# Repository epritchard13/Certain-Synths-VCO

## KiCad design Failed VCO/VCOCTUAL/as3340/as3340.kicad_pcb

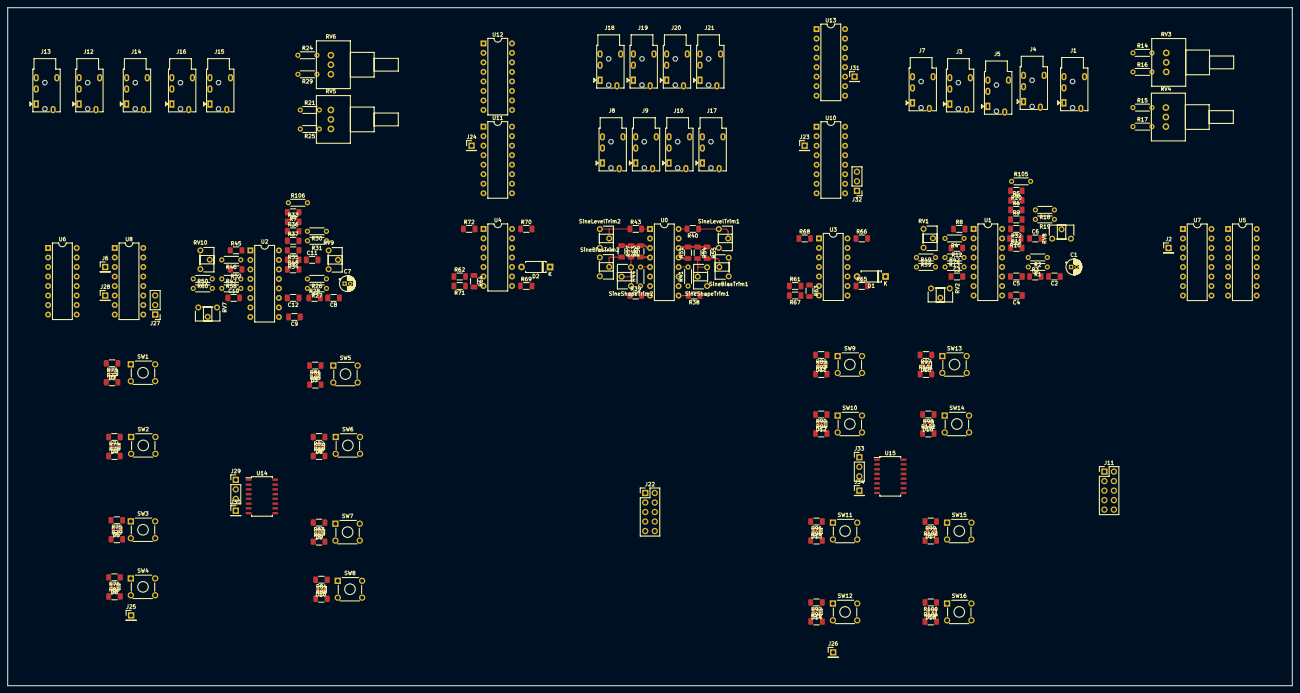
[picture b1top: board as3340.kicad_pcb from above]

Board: 2 copper layers, 342.9 x 181.0 mm, 215 parts (0 on the bottom side), 178 nets.

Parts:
C1, C7: 100nf; CP_Radial_D4.0mm_P1.50mm
C2, C6, C8, C11: 10nf; C_1206_3216Metric_Pad1.33x1.80mm_HandSolder
C3, C4, C5, C9, C10, C12: 1nf; C_1206_3216Metric_Pad1.33x1.80mm_HandSolder
D1, D2: DIODE; D_A-405_P7.62mm_Horizontal
D3, D4, D5, D6, D7, D8, D9, D10, D11, D12, D13, D14, D15, D16, D17, D18: LD271; LED_0603_1608Metric
J1, J15: LinearFMInput; Jack_3.5mm_PJ320E_Horizontal
J2, J6, J23, J24, J25, J26, J28, J30, J31, J34: Conn_01x01_Male; PinHeader_1x01_P2.54mm_Vertical
J3, J13: HardSyncInput; Jack_3.5mm_PJ320E_Horizontal
J4, J14: SoftSyncInput; Jack_3.5mm_PJ320E_Horizontal
J5, J16: CV1; Jack_3.5mm_PJ320E_Horizontal
J7, J12: PWM Input; Jack_3.5mm_PJ320E_Horizontal
J8, J18: SQR OUT; Jack_3.5mm_PJ320E_Horizontal
J9, J19: SAW OUT; Jack_3.5mm_PJ320E_Horizontal
J10, J20: TRI OUT; Jack_3.5mm_PJ320E_Horizontal
J11, J22: Conn_02x05_Odd_Even; PinHeader_2x05_P2.54mm_Vertical
J17, J21: SIN OUT; Jack_3.5mm_PJ320E_Horizontal
J27, J29, J32, J33: Conn_01x03_Male; PinHeader_1x03_P2.54mm_Vertical
R1, R18, R27, R30, R41, R44, R105, R106: 1M; R_Axial_DIN0204_L3.6mm_D1.6mm_P5.08mm_Horizontal
R2, R26: 1.5M; R_Axial_DIN0204_L3.6mm_D1.6mm_P5.08mm_Horizontal
R3, R10, R28, R34, R73, R74, R75, R76, R81, R82, R83, R84, R89, R90, R91, R92, R97, R98, R99, R100: 470; R_1206_3216Metric_Pad1.30x1.75mm_HandSolder
R4, R46: 5.6k; R_Axial_DIN0204_L3.6mm_D1.6mm_P5.08mm_Horizontal
R5, R6, R7, R9, R20, R33, R36, R37, R40, R43, R61, R62, R63, R64: 100k; R_1206_3216Metric_Pad1.30x1.75mm_HandSolder
R8, R45: 24k; R_1206_3216Metric_Pad1.30x1.75mm_HandSolder
R11, R48: 1.8k; R_1206_3216Metric_Pad1.30x1.75mm_HandSolder
R12, R52: 910; R_1206_3216Metric_Pad1.30x1.75mm_HandSolder
R13, R58: 2k; R_Axial_DIN0204_L3.6mm_D1.6mm_P5.08mm_Horizontal
R14, R21: 10k; R_Axial_DIN0204_L3.6mm_D1.6mm_P5.08mm_Horizontal
R15, R17, R19, R24, R29, R31: 100k; R_Axial_DIN0204_L3.6mm_D1.6mm_P5.08mm_Horizontal
R16, R25, R42, R47, R49, R50, R59, R60: 47k; R_Axial_DIN0204_L3.6mm_D1.6mm_P5.08mm_Horizontal
R32, R35: 200k; R_1206_3216Metric_Pad1.30x1.75mm_HandSolder
R38, R39: 4.7k; R_1206_3216Metric_Pad1.30x1.75mm_HandSolder
R51, R53, R65, R66, R67, R68, R69, R70, R71, R72: 1k; R_1206_3216Metric_Pad1.30x1.75mm_HandSolder
R54, R56: 20k; R_1206_3216Metric_Pad1.30x1.75mm_HandSolder
R55, R57: 470k; R_1206_3216Metric_Pad1.30x1.75mm_HandSolder
R77, R78, R79, R80, R85, R86, R87, R88, R93, R94, R95, R96, R101, R102, R103, R104: 10k; R_1206_3216Metric_Pad1.30x1.75mm_HandSolder
RV1, RV7, RV10: 10k Pot; Potentiometer_ACP_CA6-H2,5_Horizontal
RV2: 20k Pot; Potentiometer_ACP_CA6-H2,5_Horizontal
RV3, RV4, RV5, RV6: 100kPot; Potentiometer_Vishay_148-149_Single_Horizontal
RV8, RV9: 100k Pot; Potentiometer_ACP_CA6-H2,5_Horizontal
SW1, SW2, SW3, SW4, SW5, SW6, SW7, SW8, SW9, SW10, SW11, SW12, SW13, SW14, SW15, SW16: SW_DIP_x01; SW_TH_Tactile_Omron_B3F-10xx
SineBiasTrim1, SineBiasTrim2: 100k Pot; Potentiometer_ACP_CA6-H2,5_Horizontal
SineLevelTrim1, SineLevelTrim2: 1M Pot; Potentiometer_ACP_CA6-H2,5_Horizontal
SineShapeTrim1, SineShapeTrim2: 100k Pot; Potentiometer_ACP_CA6-H2,5_Horizontal
U0: LM13700; DIP-16_W7.62mm
U1, U2: AS3340; DIP-16_W7.62mm
U3, U4: LM324; DIP-14_W7.62mm
U5, U6, U12, U13: 74ls189; DIP-16_W7.62mm
U7, U8, U10, U11: 74HC4051; DIP-16_W7.62mm
U14, U15: 74LS138; SOIC-16W_5.3x10.2mm_P1.27mm

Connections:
+5V: J22.9, R73.2, R74.2, R75.2, R76.2, R77.1, R78.1, R79.1, R80.1, R81.2, R82.2, R83.2, R84.2, R85.1, R86.1, R87.1, R88.1, R89.2, R90.2, R91.2, R92.2, R93.1, R94.1, R95.1, R96.1, R97.2, R98.2, R99.2, R100.2, R101.1, R102.1, R103.1, R104.1, U5.16 (VCC), U6.16 (VCC), U7.16 (VCC), U8.16 (VCC), U10.16 (VCC), U11.16 (VCC), U12.16 (VCC), U13.16 (VCC), U14.16 (VCC), U15.16 (VCC)
+15V: J11.9, J11.10, R2.1, R16.2, R17.2, R25.2, R26.1, R29.2, R41.1, R44.1, RV8.3, RV9.3, SineBiasTrim1.3, SineBiasTrim2.3, SineLevelTrim1.3, SineLevelTrim2.3, U0.7, U0.10, U0.11 (V+), U1.16 (VCC), U2.16 (VCC), U3.4 (V+), U4.4 (V+)
-15V: J11.1, J11.2, R12.2, R14.1, R15.1, R21.1, R24.1, R38.1, R39.1, R52.2, SineBiasTrim1.1, SineBiasTrim2.1, U0.6 (V-), U3.11 (V-), U4.11 (V-)
GND: C2.1, C5.1, C6.2, C8.1, C11.2, C12.1, D1.1 (K), D2.1 (K), J1.S, J3.S, J4.S, J5.S, J7.S, J8.S, J9.S, J10.S, J11.3, J11.4, J11.5, J11.6, J11.7, J11.8, J12.S, J13.S, J14.S, J15.S, J16.S, J17.S, J18.S, J19.S, J20.S, J21.S, J22.2, R11.2, R48.2, R49.2, R50.2, R59.2, R60.2, R61.1, R62.1, RV2.3, RV7.3, U1.12 (GND), U2.12 (GND), U5.1 (A0), U5.2 (~CS), U5.8 (GND), U5.13 (A3), U5.14 (A2), U5.15 (A1), U6.1 (A0), U6.2 (~CS), U6.8 (GND), U6.13 (A3), U6.14 (A2), U6.15 (A1), U7.7 (VEE), U7.8 (GND), U8.7 (VEE), U8.8 (GND), U10.7 (VEE), U10.8 (GND), U11.7 (VEE), U11.8 (GND), U12.1 (A0), U12.2 (~CS), U12.8 (GND), U12.13 (A3), U12.14 (A2), U12.15 (A1), U13.1 (A0), U13.2 (~CS), U13.8 (GND), U13.13 (A3), U13.14 (A2), U13.15 (A1), U14.4 (E1), U14.5 (E2), U14.8 (GND), U15.4 (E1), U15.5 (E2), U15.8 (GND)
unnamed: C1.1, R1.1
unnamed: C1.2, J1.T, U7.15 (A2), U8.15 (A2)
unnamed: C2.2, R3.2
unnamed: C3.1, J3.T, U7.14 (A1), U8.14 (A1)
unnamed: C3.2, U1.6 (VHSI)
unnamed: C4.1, J4.T
unnamed: C4.2, U1.9 (VSSI)
unnamed: C5.2, U1.11 (CAP)
unnamed: C6.1, R10.1
unnamed: C7.1, R27.1
unnamed: C7.2, J15.T, U7.2 (A6), U8.2 (A6)
unnamed: C8.2, R28.2
unnamed: C9.1, J14.T
unnamed: C9.2, U2.9 (VSSI)
unnamed: C10.1, J13.T, U7.5 (A5), U8.5 (A5)
unnamed: C10.2, U2.6 (VHSI)
unnamed: C11.1, R34.1
unnamed: C12.2, U2.11 (CAP)
unnamed: D1.2 (A), R13.2, R59.1, U3.10 (+)
unnamed: D2.2 (A), R58.2, R60.1, U4.10 (+)
unnamed: D3.1 (K), SW1.1, U14.15 (O0)
unnamed: D3.2 (A), R73.1
unnamed: D4.1 (K), SW2.1, U14.14 (O1)
unnamed: D4.2 (A), R74.1
unnamed: D5.1 (K), SW3.1, U14.13 (O2)
unnamed: D5.2 (A), R75.1
unnamed: D6.1 (K), SW4.1, U14.12 (O3)
unnamed: D6.2 (A), R76.1
unnamed: D7.1 (K), SW5.1, U14.11 (O4)
unnamed: D7.2 (A), R81.1
unnamed: D8.1 (K), SW6.1, U14.10 (O5)
unnamed: D8.2 (A), R82.1
unnamed: D9.1 (K), SW7.1, U14.9 (O6)
unnamed: D9.2 (A), R83.1
unnamed: D10.1 (K), SW8.1, U14.7 (O7)
unnamed: D10.2 (A), R84.1
unnamed: D11.1 (K), SW9.1, U15.15 (O0)
unnamed: D11.2 (A), R89.1
unnamed: D12.1 (K), SW10.1, U15.14 (O1)
unnamed: D12.2 (A), R90.1
unnamed: D13.1 (K), SW11.1, U15.13 (O2)
unnamed: D13.2 (A), R91.1
unnamed: D14.1 (K), SW12.1, U15.12 (O3)
unnamed: D14.2 (A), R92.1
unnamed: D15.1 (K), SW13.1, U15.11 (O4)
unnamed: D15.2 (A), R97.1
unnamed: D16.1 (K), SW14.1, U15.10 (O5)
unnamed: D16.2 (A), R98.1
unnamed: D17.1 (K), SW15.1, U15.9 (O6)
unnamed: D17.2 (A), R99.1
unnamed: D18.1 (K), SW16.1, U15.7 (O7)
unnamed: D18.2 (A), R100.1
unnamed: J2.1, U7.3 (A)
unnamed: J5.T, R5.2
unnamed: J6.1, U8.3 (A)
unnamed: J7.T, R42.1, U7.13 (A0), U8.13 (A0)
unnamed: J8.T, R65.2, U10.4 (A7), U11.4 (A7)
unnamed: J9.T, R66.2, U10.2 (A6), U11.2 (A6)
unnamed: J10.T, R67.2, U10.5 (A5), U11.5 (A5)
unnamed: J12.T, R47.1, U7.1 (A4), U8.1 (A4)
unnamed: J16.T, R33.2
unnamed: J17.T, R68.2, U10.1 (A4), U11.1 (A4)
unnamed: J18.T, R69.2, U10.12 (A3), U11.12 (A3)
unnamed: J19.T, R70.2, U10.15 (A2), U11.15 (A2)
unnamed: J20.T, R71.2, U10.14 (A1), U11.14 (A1)
unnamed: J21.T, R72.2, U10.13 (A0), U11.13 (A0)
unnamed: J22.1, U12.3 (~WE)
unnamed: J22.3, U6.3 (~WE)
unnamed: J22.4, U5.12 (D4), U6.12 (D4), U12.12 (D4), U13.12 (D4)
unnamed: J22.5, U13.3 (~WE)
unnamed: J22.6, U5.10 (D3), U6.10 (D3), U12.10 (D3), U13.10 (D3)
unnamed: J22.7, U5.3 (~WE)
unnamed: J22.8, U5.6 (D2), U6.6 (D2), U12.6 (D2), U13.6 (D2)
unnamed: J22.10, U5.4 (D1), U6.4 (D1), U12.4 (D1), U13.4 (D1)
unnamed: J23.1, U10.3 (A)
unnamed: J24.1, U11.3 (A)
unnamed: J25.1, R77.2, R78.2, R79.2, R80.2, R85.2, R86.2, R87.2, R88.2, SW1.2, SW2.2, SW3.2, SW4.2, SW5.2, SW6.2, SW7.2, SW8.2
unnamed: J26.1, R93.2, R94.2, R95.2, R96.2, R101.2, R102.2, R103.2, R104.2, SW9.2, SW10.2, SW11.2, SW12.2, SW13.2, SW14.2, SW15.2, SW16.2
unnamed: J27.1, U6.9 (~Y3), U8.9 (S2)
unnamed: J27.2, U6.7 (~Y2), U8.10 (S1)
unnamed: J27.3, U6.5 (~Y1), U8.11 (S0)
unnamed: J28.1, U6.11 (~Y4), U8.6 (~E)
unnamed: J29.1, U14.1 (A0)
unnamed: J29.2, U14.2 (A1)
unnamed: J29.3, U14.3 (A2)
unnamed: J30.1, U14.6 (E3)
unnamed: J31.1, U10.6 (~E), U13.11 (~Y4)
unnamed: J32.1, U10.9 (S2), U13.9 (~Y3)
unnamed: J32.2, U10.10 (S1), U13.7 (~Y2)
unnamed: J32.3, U10.11 (S0), U13.5 (~Y1)
unnamed: J33.1, U15.1 (A0)
unnamed: J33.2, U15.2 (A1)
unnamed: J33.3, U15.3 (A2)
unnamed: J34.1, U15.6 (E3)
unnamed: R1.2, R2.2, R3.1, U1.13 (VLFI)
unnamed: R4.2, U1.2 (SCALE2)
unnamed: R7.1, U7.4 (A7), U8.4 (A7)
unnamed: R8.1, RV1.1
unnamed: R8.2, U1.1 (SCALE1)
unnamed: R5.1, R6.1, R9.1, R10.2, R20.2, R32.2, R105.1, U1.15 (VFCI)
unnamed: R11.1, U1.14 (VS)
unnamed: R4.1, R12.1, RV1.2, RV1.3, U1.3 (VEE)
unnamed: R13.1, U1.4 (VP)
unnamed: R14.2, RV3.3
unnamed: R15.2, RV4.3
unnamed: R16.1, RV3.1
unnamed: R17.1, RV4.1
unnamed: R18.1, RV4.2
unnamed: R6.2, R18.2
unnamed: R19.1, RV3.2
unnamed: R9.2, R19.2
unnamed: R20.1, U7.12 (A3), U8.12 (A3)
unnamed: R21.2, RV5.3
unnamed: R24.2, RV6.3
unnamed: R25.1, RV5.1
unnamed: R26.2, R27.2, R28.1, U2.13 (VLFI)
unnamed: R29.1, RV6.1
unnamed: R30.1, RV6.2
unnamed: R30.2, R36.2
unnamed: R31.1, RV5.2
unnamed: R31.2, R37.2
unnamed: R32.1, RV8.1, RV8.2
unnamed: R7.2, R33.1, R34.2, R35.2, R36.1, R37.1, R106.1, U2.15 (VFCI)
unnamed: R35.1, RV9.1, RV9.2
unnamed: R39.2, U0.8, U4.3 (+)
unnamed: R40.1, SineLevelTrim1.1, SineLevelTrim1.2
unnamed: R40.2, U0.16
unnamed: R41.2, U0.12
unnamed: R42.2, R49.1, U1.5 (VPWM)
unnamed: R43.1, SineLevelTrim2.1, SineLevelTrim2.2
unnamed: R43.2, U0.1
unnamed: R44.2, U0.5
unnamed: R45.1, RV10.1
unnamed: R45.2, U2.1 (SCALE1)
unnamed: R46.1, R52.1, RV10.2, RV10.3, U2.3 (VEE)
unnamed: R46.2, U2.2 (SCALE2)
unnamed: R47.2, R50.1, U2.5 (VPWM)
unnamed: R48.1, U2.14 (VS)
unnamed: R51.1, U0.13 (-)
unnamed: R51.2, R54.1, R55.1, U0.14 (+)
unnamed: R53.1, U0.4 (-)
unnamed: R53.2, R56.1, R57.1, U0.3 (+)
unnamed: R54.2, SineShapeTrim1.2, SineShapeTrim1.3
unnamed: R55.2, SineBiasTrim1.2
unnamed: R56.2, SineShapeTrim2.2, SineShapeTrim2.3
unnamed: R57.2, SineBiasTrim2.2
unnamed: R58.1, U2.4 (VP)
unnamed: R61.2, R63.1, U3.6 (-)
unnamed: R62.2, R64.1, U4.6 (-)
unnamed: R63.2, R67.1, SineShapeTrim1.1, U3.7
unnamed: R64.2, R71.1, SineShapeTrim2.1, U4.7
unnamed: R65.1, U3.8, U3.9 (-)
unnamed: R66.1, U3.13 (-), U3.14
unnamed: R68.1, U3.1, U3.2 (-)
unnamed: R69.1, U4.8, U4.9 (-)
unnamed: R70.1, U4.13 (-), U4.14
unnamed: R72.1, U4.1, U4.2 (-)
unnamed: RV2.1, U1.7 (VHFT)
unnamed: R105.2, RV2.2
unnamed: RV7.1, U2.7 (VHFT)
unnamed: R106.2, RV7.2
unnamed: U1.8 (VSO), U3.12 (+)
unnamed: U1.10 (VTO), U3.5 (+)
unnamed: U2.8 (VSO), U4.12 (+)
unnamed: U2.10 (VTO), U4.5 (+)
unnamed: R38.2, U0.9, U3.3 (+)
unnamed: U5.5 (~Y1), U7.11 (S0)
unnamed: U5.7 (~Y2), U7.10 (S1)
unnamed: U5.9 (~Y3), U7.9 (S2)
unnamed: U5.11 (~Y4), U7.6 (~E)
unnamed: U11.6 (~E), U12.11 (~Y4)
unnamed: U11.9 (S2), U12.9 (~Y3)
unnamed: U11.10 (S1), U12.7 (~Y2)
unnamed: U11.11 (S0), U12.5 (~Y1)

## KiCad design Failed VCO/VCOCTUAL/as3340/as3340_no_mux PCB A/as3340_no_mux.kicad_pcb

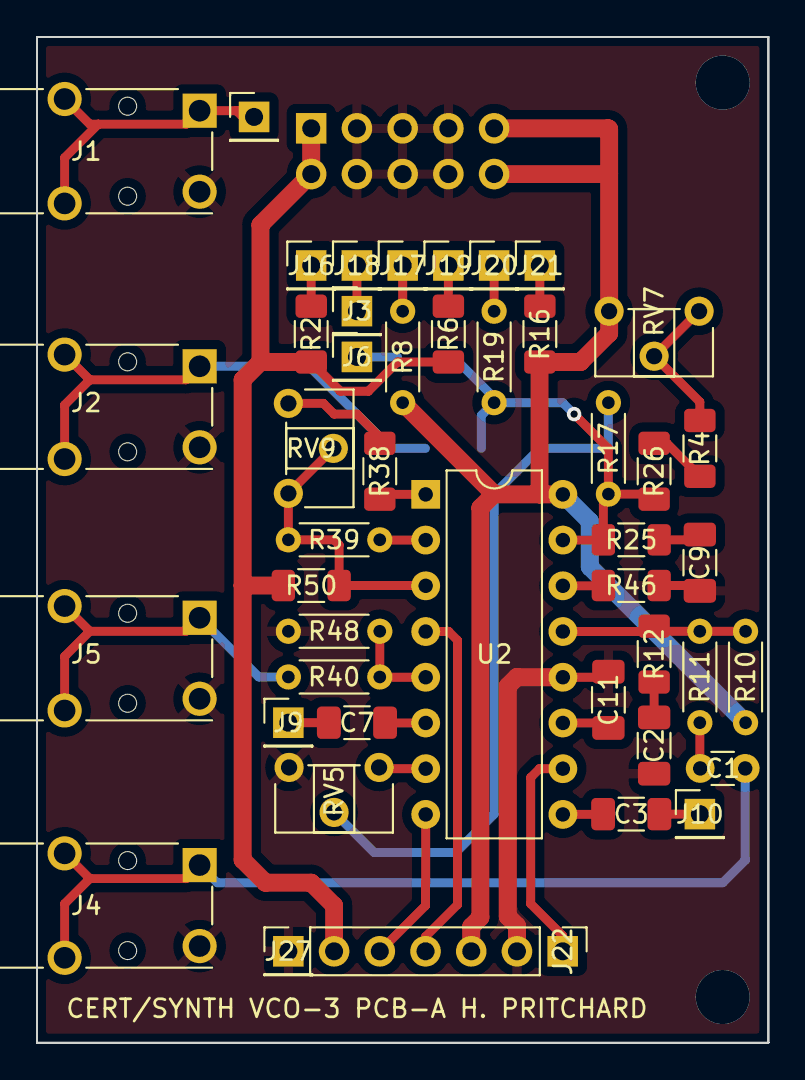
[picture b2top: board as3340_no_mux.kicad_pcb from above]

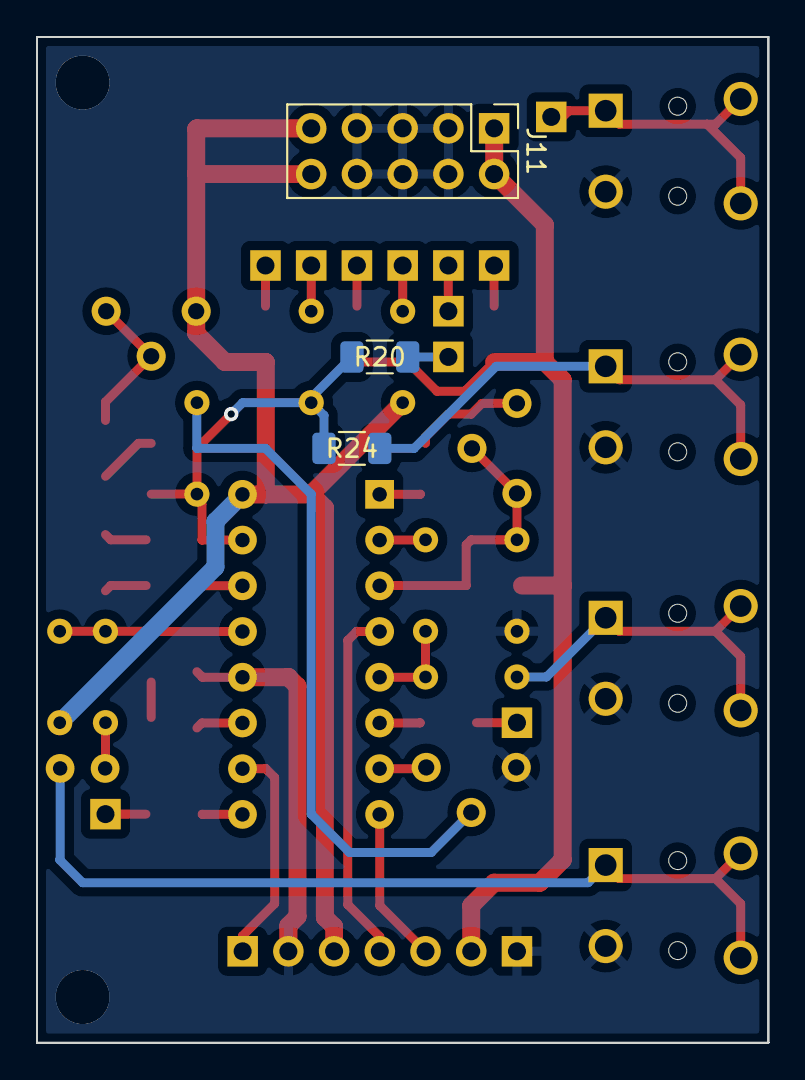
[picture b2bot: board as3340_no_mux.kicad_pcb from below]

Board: 2 copper layers, 40.6 x 55.9 mm, 48 parts (3 on the bottom side), 37 nets.

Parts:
C1: 100nf; C_Disc_D3.0mm_W1.6mm_P2.50mm
C2, C9: 10nf; C_1206_3216Metric_Pad1.33x1.80mm_HandSolder
C3, C7, C11: 1nf; C_1206_3216Metric_Pad1.33x1.80mm_HandSolder
J1: Sync INput; Jack_3.5mm_Switronic_ST-005-G_horizontal
J2: CV1; Jack_3.5mm_Switronic_ST-005-G_horizontal
J3, J6, J9, J10, J16, J17, J18, J19, J20, J21, J25, J27: Conn_01x01_Male; PinHeader_1x01_P2.54mm_Vertical
J4: LinearFmINput; Jack_3.5mm_Switronic_ST-005-G_horizontal
J5: PWM INput; Jack_3.5mm_Switronic_ST-005-G_horizontal
J11: Conn_02x05_Odd_Even; PinHeader_2x05_P2.54mm_Vertical
J22: Conn_01x06_Female; PinHeader_1x06_P2.54mm_Vertical
R2: 10k; R_1206_3216Metric_Pad1.30x1.75mm_HandSolder
R4, R6, R16, R20, R24, R26: 100k; R_1206_3216Metric_Pad1.30x1.75mm_HandSolder
R8, R40, R48: 47k; R_Axial_DIN0204_L3.6mm_D1.6mm_P5.08mm_Horizontal
R10: 1.5M; R_Axial_DIN0204_L3.6mm_D1.6mm_P5.08mm_Horizontal
R11, R17, R19: 1M; R_Axial_DIN0204_L3.6mm_D1.6mm_P5.08mm_Horizontal
R12, R25: 470; R_1206_3216Metric_Pad1.30x1.75mm_HandSolder
R38: 24k; R_1206_3216Metric_Pad1.30x1.75mm_HandSolder
R39: 5.6k; R_Axial_DIN0204_L3.6mm_D1.6mm_P5.08mm_Horizontal
R46: 1.8k; R_1206_3216Metric_Pad1.30x1.75mm_HandSolder
R50: 910; R_1206_3216Metric_Pad1.30x1.75mm_HandSolder
RV5: 20k Pot; Potentiometer_ACP_CA6-H2,5_Horizontal
RV7: 100k TrimPot; Potentiometer_ACP_CA6-H2,5_Horizontal
RV9: 10k Pot; Potentiometer_ACP_CA6-H2,5_Horizontal
U2: AS3340; DIP-16_W7.62mm

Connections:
+15V: J11.9, J11.10, J22.3, R8.2, R10.1, R16.2, RV7.3, U2.16 (VCC)
-15V: J11.1, J11.2, J22.6, R2.1, R6.1, R50.2
GND: C2.1, C9.2, C11.1, J1.S, J2.S, J4.S, J5.S, J11.3, J11.4, J11.5, J11.6, J11.7, J11.8, J22.2, J27.1, R46.2, R48.2, RV5.3, U2.12 (GND)
unnamed: C1.1, R11.1
unnamed: C1.2, J4.R, J4.T
unnamed: C2.2, R12.2
unnamed: C3.1, J10.1
unnamed: C3.2, U2.9 (VSSI)
unnamed: C7.1, J9.1
unnamed: C7.2, U2.6 (VHSI)
unnamed: C9.1, R25.1
unnamed: C11.2, U2.11 (CAP)
unnamed: J1.R, J1.T, J25.1
unnamed: J3.1, J18.1
unnamed: J22.1, U2.10 (VTO)
unnamed: J22.4, U2.4 (VP)
unnamed: J22.5, U2.8 (VSO)
unnamed: J16.1, R2.2
unnamed: J19.1, R6.2
unnamed: J17.1, R8.1
unnamed: R10.2, R11.2, R12.1, U2.13 (VLFI)
unnamed: J21.1, R16.1
unnamed: R17.1, R19.2, R20.2, R24.1, R25.2, R26.2, U2.15 (VFCI)
unnamed: R17.2, RV5.2
unnamed: J20.1, R19.1
unnamed: J6.1, R20.1
unnamed: J2.R, J2.T, R24.2
unnamed: R4.2, R26.1
unnamed: R38.1, RV9.1
unnamed: R38.2, U2.1 (SCALE1)
unnamed: R39.1, R50.1, RV9.2, RV9.3, U2.3 (VEE)
unnamed: R39.2, U2.2 (SCALE2)
unnamed: J5.R, J5.T, R40.1
unnamed: R40.2, R48.1, U2.5 (VPWM)
unnamed: R46.1, U2.14 (VS)
unnamed: RV5.1, U2.7 (VHFT)
unnamed: R4.1, RV7.1, RV7.2

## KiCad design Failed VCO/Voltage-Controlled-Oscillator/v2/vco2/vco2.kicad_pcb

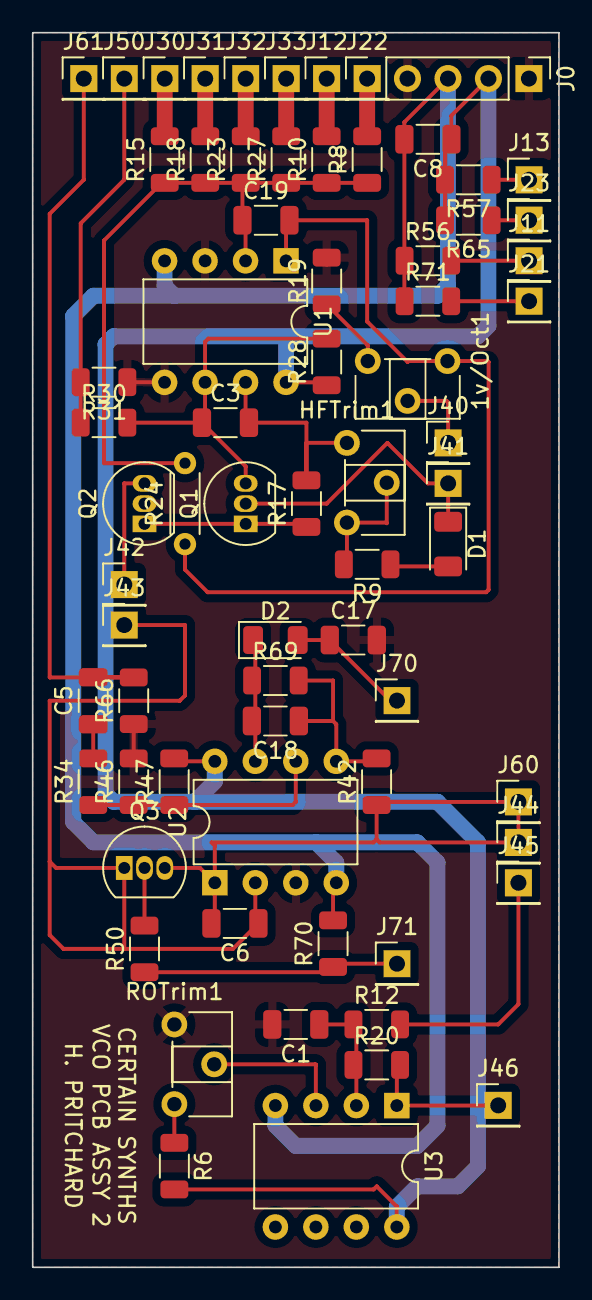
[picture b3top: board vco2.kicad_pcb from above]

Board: 2 copper layers, 33.0 x 77.5 mm, 70 parts (0 on the bottom side), 37 nets.

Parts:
1v/Oct1: 100; Potentiometer_ACP_CA6-H2,5_Horizontal
C1: 0.1uF; C_1206_3216Metric
C3, C17, C19: 100pF; C_1206_3216Metric
C5: 0.001uF; C_1206_3216Metric
C6: 0.005uF; C_1206_3216Metric
C8: .1uF; C_1206_3216Metric
C18: 4.7pF; C_1206_3216Metric
D1, D2: DIODE; D_1206_3216Metric
HFTrim1: 100k; Potentiometer_ACP_CA6-H2,5_Horizontal
J0: P; PinHeader_1x04_P2.54mm_Vertical
J11: TP1-; PinHeader_1x01_P2.54mm_Vertical
J12: P1; PinHeader_1x01_P2.54mm_Vertical
J13: TP1+; PinHeader_1x01_P2.54mm_Vertical
J21: TP2-; PinHeader_1x01_P2.54mm_Vertical
J22: P2; PinHeader_1x01_P2.54mm_Vertical
J23: TP2+; PinHeader_1x01_P2.54mm_Vertical
J30, J31, J32, J33: CV; PinHeader_1x01_P2.54mm_Vertical
J40: LINOUT; PinHeader_1x01_P2.54mm_Vertical
J41: LININ; PinHeader_1x01_P2.54mm_Vertical
J42: EXPOUT; PinHeader_1x01_P2.54mm_Vertical
J43: EXPIN; PinHeader_1x01_P2.54mm_Vertical
J44: RAWOUT; PinHeader_1x01_P2.54mm_Vertical
J45: RAWIN; PinHeader_1x01_P2.54mm_Vertical
J46: RAMPOUT; PinHeader_1x01_P2.54mm_Vertical
J50: LA; PinHeader_1x01_P2.54mm_Vertical
J60: RAW; PinHeader_1x01_P2.54mm_Vertical
J61: S; PinHeader_1x01_P2.54mm_Vertical
J70, J71: JUMPER00; PinHeader_1x01_P2.54mm_Vertical
Q1, Q2, Q3: 2N3904; TO-92_Inline
R6, R10, R15, R18, R23, R27, R31, R50, R66: 100k; R_1206_3216Metric
R8, R28, R30, R69: 1M; R_1206_3216Metric
R9: 4.7k; R_1206_3216Metric
R12, R17, R42, R47, R71: 10k; R_1206_3216Metric
R19: 475; R_1206_3216Metric
R20, R65: 47k; R_1206_3216Metric
R24: 100k TEMPCO; R_Axial_DIN0204_L3.6mm_D1.6mm_P5.08mm_Horizontal
R34: 1k; R_1206_3216Metric
R46: 2k; R_1206_3216Metric
R56, R57: 200k; R_1206_3216Metric
R70: 18k; R_1206_3216Metric
ROTrim1: 10k; Potentiometer_ACP_CA6-H2,5_Horizontal
U1, U2, U3: LM358; DIP-8_W7.62mm

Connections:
+12V: C6.1, C8.1, J0.2, J42.1, J43.1, J46.1, Q2.3 (C), Q3.1 (E), R6.2, R20.2, R28.1, R47.2, R57.2, R65.2, U1.8 (V+), U2.2 (-), U2.8 (V+), U3.1, U3.8 (V+)
-12V: C8.2, J0.3, R56.1, R70.2, R71.1, U1.4 (V-), U2.4 (V-), U3.4 (V-)
GND: C1.2, C17.2, J0.1, J0.4, Q2.2 (B), R19.2, R31.1, R46.2, R66.1, ROTrim1.1, U1.3 (+), U1.5 (+), U2.3 (+)
unnamed: C5.2, J61.1, R66.2
unnamed: C17.1, D2.2 (A), J70.1
unnamed: C18.2, D2.1 (K), R69.1, U2.7
unnamed: 1v/Oct1.1, C19.2, R24.1, U1.1
unnamed: D1.1 (K), J41.1, Q1.2 (B)
unnamed: C3.2, HFTrim1.1, R17.2, U1.7
unnamed: HFTrim1.2, HFTrim1.3, R9.2
unnamed: J12.1, R10.2
unnamed: J22.1, R8.2
unnamed: J30.1, R15.2
unnamed: J31.1, R18.2
unnamed: J32.1, R23.2
unnamed: J33.1, R27.2
unnamed: 1v/Oct1.2, J40.1
unnamed: C3.1, Q1.3 (C), R28.2, R30.2, U1.6 (-)
unnamed: Q1.1 (E), Q2.1 (E), R17.1
unnamed: Q3.2 (B), R50.2
unnamed: C19.1, R8.1, R10.1, R15.1, R18.1, R23.1, R24.2, R27.1, U1.2 (-)
unnamed: D1.2 (A), R9.1
unnamed: J45.1, R12.2
unnamed: 1v/Oct1.3, R19.1
unnamed: J50.1, R30.1, R31.2
unnamed: C5.1, R34.2
unnamed: C18.1, R42.2, R69.2, U2.5 (+)
unnamed: J71.1, R50.1, R70.1
unnamed: J11.1, R56.2
unnamed: J13.1, R57.1
unnamed: J23.1, R65.1
unnamed: J21.1, R71.2
unnamed: R6.1, ROTrim1.3
unnamed: C6.2, J44.1, J60.1, Q3.3 (C), R42.1, U2.1
unnamed: R34.1, R46.1, R47.1, U2.6 (-)
unnamed: C1.1, R12.1, R20.1, U3.2 (-)
unnamed: ROTrim1.2, U3.3 (+)

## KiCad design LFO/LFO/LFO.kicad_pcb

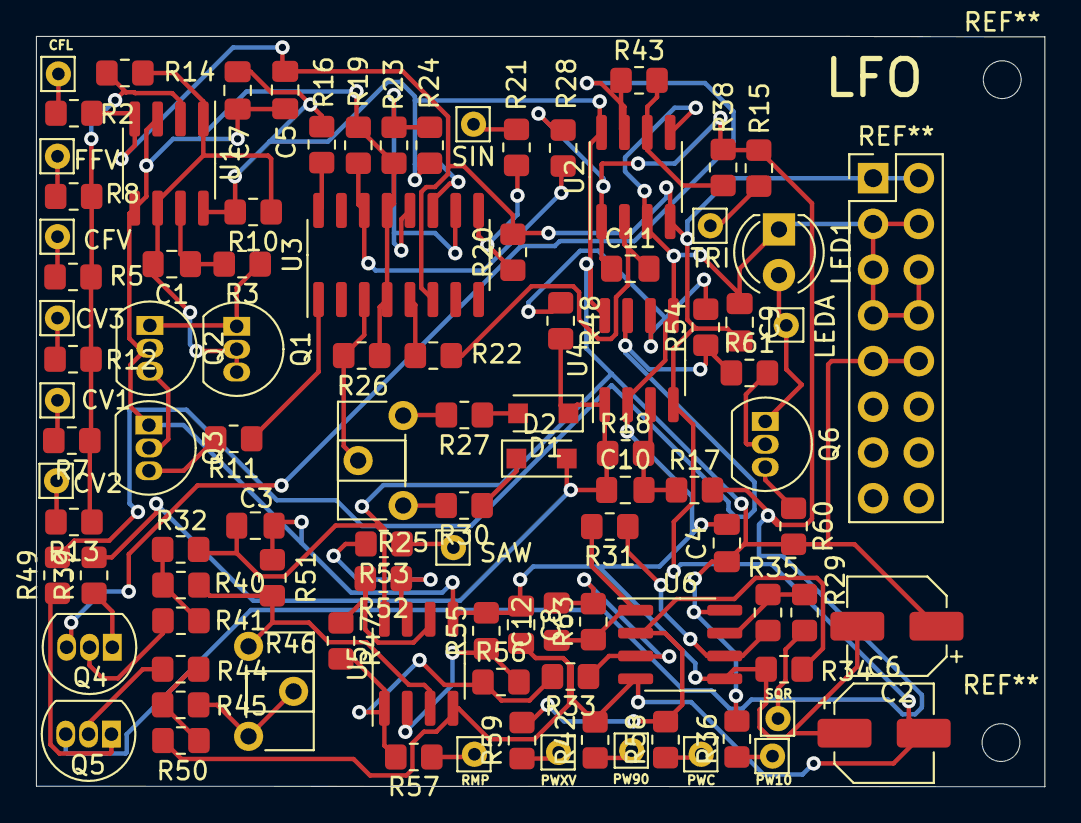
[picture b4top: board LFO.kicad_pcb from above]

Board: 2 copper layers, 56.0 x 41.7 mm, 100 parts (0 on the bottom side), 63 nets.

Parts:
C1: 100pF; C_0805_2012Metric_Pad1.18x1.45mm_HandSolder
C2, C6: 10uF; CP_Elec_5x5.9
C3, C4, C5, C7, C8, C9: .1uF; C_0805_2012Metric_Pad1.18x1.45mm_HandSolder
C10, C12: 10pF; C_0805_2012Metric_Pad1.18x1.45mm_HandSolder
C11: .02uF; C_0805_2012Metric_Pad1.18x1.45mm_HandSolder
CFL: Conn_01x01_Male; Pin_D0.7mm_L6.5mm_W1.8mm_FlatFork
CFV: Conn_01x01_Male; Pin_D0.7mm_L6.5mm_W1.8mm_FlatFork
CV1, CV2, CV3: Conn_01x01_Male; Pin_D0.7mm_L6.5mm_W1.8mm_FlatFork
D1, D2: 1N914; D_SOD-123F
FFV: Conn_01x01_Male; Pin_D0.7mm_L6.5mm_W1.8mm_FlatFork
LED1: LED; LED_D4.0mm
LEDA: Conn_01x01_Male; Pin_D0.7mm_L6.5mm_W1.8mm_FlatFork
PW10, PW90: Conn_01x01_Male; Pin_D0.7mm_L6.5mm_W1.8mm_FlatFork
PWC: Conn_01x01_Male; Pin_D0.7mm_L6.5mm_W1.8mm_FlatFork
PWXV: Conn_01x01_Male; Pin_D0.7mm_L6.5mm_W1.8mm_FlatFork
Q1, Q2, Q6: 2N3904; TO-92_Inline
Q3: 2N3906; TO-92_Inline
Q4, Q5: BF245A; TO-92_Inline
R2, R20, R60: 4.7K; R_0805_2012Metric_Pad1.20x1.40mm_HandSolder
R3, R11, R35, R40, R41, R44, R47, R51, R52, R58, R59: 10K; R_0805_2012Metric_Pad1.20x1.40mm_HandSolder
R5, R7, R12, R13, R27, R30, R33, R36, R42, R56, R61: 100K; R_0805_2012Metric_Pad1.20x1.40mm_HandSolder
R8: 3M; R_0805_2012Metric_Pad1.20x1.40mm_HandSolder
R10, R63: 4.7M; R_0805_2012Metric_Pad1.20x1.40mm_HandSolder
R14, R19: 2K; R_0805_2012Metric_Pad1.20x1.40mm_HandSolder
R15, R21, R26, R29, R53, R57: 1K; R_0805_2012Metric_Pad1.20x1.40mm_HandSolder
R16: 680K; R_0805_2012Metric_Pad1.20x1.40mm_HandSolder
R17: 120K; R_0805_2012Metric_Pad1.20x1.40mm_HandSolder
R18: 270K; R_0805_2012Metric_Pad1.20x1.40mm_HandSolder
R22: 39K; R_0805_2012Metric_Pad1.20x1.40mm_HandSolder
R23: 180K; R_0805_2012Metric_Pad1.20x1.40mm_HandSolder
R24: 2M; R_0805_2012Metric_Pad1.20x1.40mm_HandSolder
R25: 100K; Potentiometer_ACP_CA6-H2,5_Horizontal
R28: 110K; R_0805_2012Metric_Pad1.20x1.40mm_HandSolder
R31: 27K; R_0805_2012Metric_Pad1.20x1.40mm_HandSolder
R32, R50: 15K; R_0805_2012Metric_Pad1.20x1.40mm_HandSolder
R34: 1M; R_0805_2012Metric_Pad1.20x1.40mm_HandSolder
R38, R43: 20K; R_0805_2012Metric_Pad1.20x1.40mm_HandSolder
R39, R49: 30K; R_0805_2012Metric_Pad1.20x1.40mm_HandSolder
R45: 9.1K; R_0805_2012Metric_Pad1.20x1.40mm_HandSolder
R46: 2K; Potentiometer_ACP_CA6-H2,5_Horizontal
R48, R54, R55: 47K; R_0805_2012Metric_Pad1.20x1.40mm_HandSolder
RMP: Conn_01x01_Male; Pin_D0.7mm_L6.5mm_W1.8mm_FlatFork
SAW: Conn_01x01_Male; Pin_D0.7mm_L6.5mm_W1.8mm_FlatFork
SIN: Conn_01x01_Male; Pin_D0.7mm_L6.5mm_W1.8mm_FlatFork
SQR: Conn_01x01_Male; Pin_D0.7mm_L6.5mm_W1.8mm_FlatFork
TRI: Conn_01x01_Male; Pin_D0.7mm_L6.5mm_W1.8mm_FlatFork
U1: TL072; SOIC-8_3.9x4.9mm_P1.27mm
U2, U4, U5, U6: TL082; SOIC-8_3.9x4.9mm_P1.27mm
U3: LM13700; SOIC-16_3.9x9.9mm_P1.27mm

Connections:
+12V: C2.1, C3.1, C4.1, C5.1, R10.2, R16.2, R24.1, R32.1, R36.2, R60.2, U1.8, U2.8, U3.11, U4.8, U5.8, U6.8
-12V: C6.2, C7.2, C8.2, C9.2, R2.1, R20.2, R42.2, R50.2, U1.4, U2.4, U3.6, U4.4, U5.4, U6.4
/CFL: CFL.1, R2.2
/CFV: CFV.1, R5.2
/CV1: CV1.1, R7.2
/CV2: CV2.1, R13.2
/CV3: CV3.1, R12.2
/FFV: FFV.1, R8.2
/LEDA: LED1.2, LEDA.1, Q6.1
/PW10: PW10.1, R36.1
/PW90: PW90.1, R42.1
/PWC: PWC.1, R58.1
/PWXV: PWXV.1, R59.1
/RMP: R57.1, RMP.1
/SAW: R53.1, SAW.1
/SIN: R21.1, SIN.1
/SQR: R29.1, SQR.1
/TRI: R15.1, TRI.1
GNDREF: C2.2, C3.2, C4.2, C5.2, C6.1, C7.1, C8.1, C9.1, LED1.1, Q2.2, Q3.1, R19.2, R23.2, R26.2, R34.1, R51.2, R55.2, U1.3, U1.5, U2.3, U2.5, U3.4, U3.13, U4.2, U4.5, U5.5, U6.5
unnamed: C1.1, R3.2, U1.7
unnamed: C1.2, Q1.2, Q1.3, R10.1, R14.1, U1.1, U1.6
unnamed: C10.1, D1.1, D2.2, R18.1, R39.2, R48.2, U4.1
unnamed: C10.2, R17.1, R18.2, U4.3
unnamed: C11.1, Q5.3, R15.2, R17.2, R28.2, R38.2, U2.1
unnamed: C11.2, R22.1, U2.2
unnamed: C12.1, R31.2, R63.1, U6.1
unnamed: C12.2, R33.1, R63.2, U6.3
unnamed: D1.2, R27.2
unnamed: D2.1, R30.1
unnamed: Q1.1, Q2.1, R3.1
unnamed: Q2.3, Q3.2
unnamed: Q3.3, R11.2
unnamed: Q4.1, R39.1
unnamed: Q4.2, R41.2
unnamed: Q4.3, R43.1, U2.7
unnamed: Q5.1, R49.1
unnamed: Q5.2, R44.2
unnamed: Q6.2, R61.2
unnamed: Q6.3, R60.1
unnamed: R11.1, U3.1
unnamed: R5.1, R7.1, R8.1, R12.1, R13.1, R14.2, U1.2
unnamed: R16.1, U3.16
unnamed: R19.1, R28.1, U3.14
unnamed: R20.1, R21.2, U3.9
unnamed: R22.2, U3.5
unnamed: R23.1, R24.2, U3.10, U3.12
unnamed: R25.1, R30.2
unnamed: R25.2, R26.1, U3.3
unnamed: R25.3, R27.1
unnamed: R29.2, R35.1, U6.7
unnamed: R31.1, R35.2, U6.6
unnamed: R32.2, R40.2, R41.1
unnamed: R33.2, R47.2, R56.1, R57.2, U5.1
unnamed: R34.2, R58.2, R59.2, U6.2
unnamed: R38.1, R43.2, U2.6
unnamed: R40.1, R46.1, R51.1, U5.3
unnamed: R44.1, R45.2, R50.1
unnamed: R45.1, R46.2, R46.3
unnamed: R47.1, R52.2, U5.6
unnamed: R48.1, R54.2, U4.6
unnamed: R49.2, R54.1, R61.1, U4.7
unnamed: R52.1, R53.2, U5.7
unnamed: R55.1, R56.2, U5.2
